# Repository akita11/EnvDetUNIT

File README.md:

# Envelope Detector (包絡線検波UNIT)

アナログ信号波形の包絡線（波形の外側の波形）を生成します。マイクなどからの音声信号の振幅を計測する場合などに便利です。Grove端子または3ピン端子で、マイク等の信号源とM5Stack等のマイコンとの間に接続して使用します。（[スイッチサイエンスで委託販売中](https://www.switch-science.com/products/9043)です）

表面

裏面

左側（CN1・J1、矢印の根本側）から信号源（マイクアンプの出力）を接続し、右側（CN2・J2、矢印の先端側）に包絡線波形が出力されるので、マイコン等に接続します。

## ピン配置

電源はCN1/J1/CN2/J2のいずれからのVDDへ+3.3V〜+5Vを与える。

### 入力側

- CN1(Groveコネクタ): アナログ入力1/アナログ入力2/VDD/GND （信号入力は標準で「アナログ入力1」で、JP1で「アナログ入力2」に切り替え可能
- J1（2.54mmピンヘッダ3ピン）: VDD/GND/アナログ入力

### 出力側

- CN2(Groveコネクタ): アナログ出力1/アナログ出力2/VDD/GND （信号出力は標準で「アナログ出力1」で、JP2で「アナログ出力2」に切り替え可能
- J2（2.54mmピンヘッダ3ピン）: VDD/GND/アナログ出力

## 包絡線検波とは？

音声信号などの変化が速い信号をマイコン等のA/D変換で取得する場合、A/D変換のタイミングと信号波形の変化のタイミングがあわないと、A/D変換値が波形の山の部分や谷の部分をバラバラに拾ってしまい（図中の◯）、正しく振幅を取得できません。

信号波形を包絡線検波回路に与えると、信号波形の外側をつないだ「包絡線」をつくることができます。（包絡線検波回路は、ダイオードを用いる半波整流回路にコンデンサの平滑回路を組み合わせたもの。厳密にはコンデンサの容量によって包絡線の波形が少し変わる。なおこのUNITでは、特に小さい振幅の信号も正しく扱えるようにオペアンプを使った理想ダイオードを使っています）

このようにして得られた包絡線波形に対してA/D変換を行えば、（ほぼ）正しく信号波形の振幅を取得することができます。

実際のマイク（M5StackマイクUNIT）の波形（黄色）と、このUNITの出力（水色）。

※なおこの回路の出力インピーダンスは高めなので、抵抗などの低インピーダンスの負荷を駆動すると波形が歪むことがあります。必要に応じて出力側にバッファ（ボルテージフォロア等）を使用してください。

## （オプション）時定数の調整

包絡線検波の回路の特性上、入力する信号波形の周波数によっては正しく包絡線を得られない場合があります。標準設定では1kHz前後の音声帯域の信号では、ほぼ正しい包絡線を得られますが、必要であれば回路の特性（時定数）を変更することができます。JP3をカットし、J3（2.54mmピンヘッダ2ピン）に適当な容量のコンデンサを接続します。標準では10uF（時定数は約160Hz）で、これより大きな容量のコンデンサを接続すると、包絡線の変化がより緩やかになります。

Aoutに100uFのコンデンサを接続したときの、マイクの波形（黄色）と、このUNITの出力（水色）。

## Author

Junichi Akita (akita@ifdl.jp, @akita11)

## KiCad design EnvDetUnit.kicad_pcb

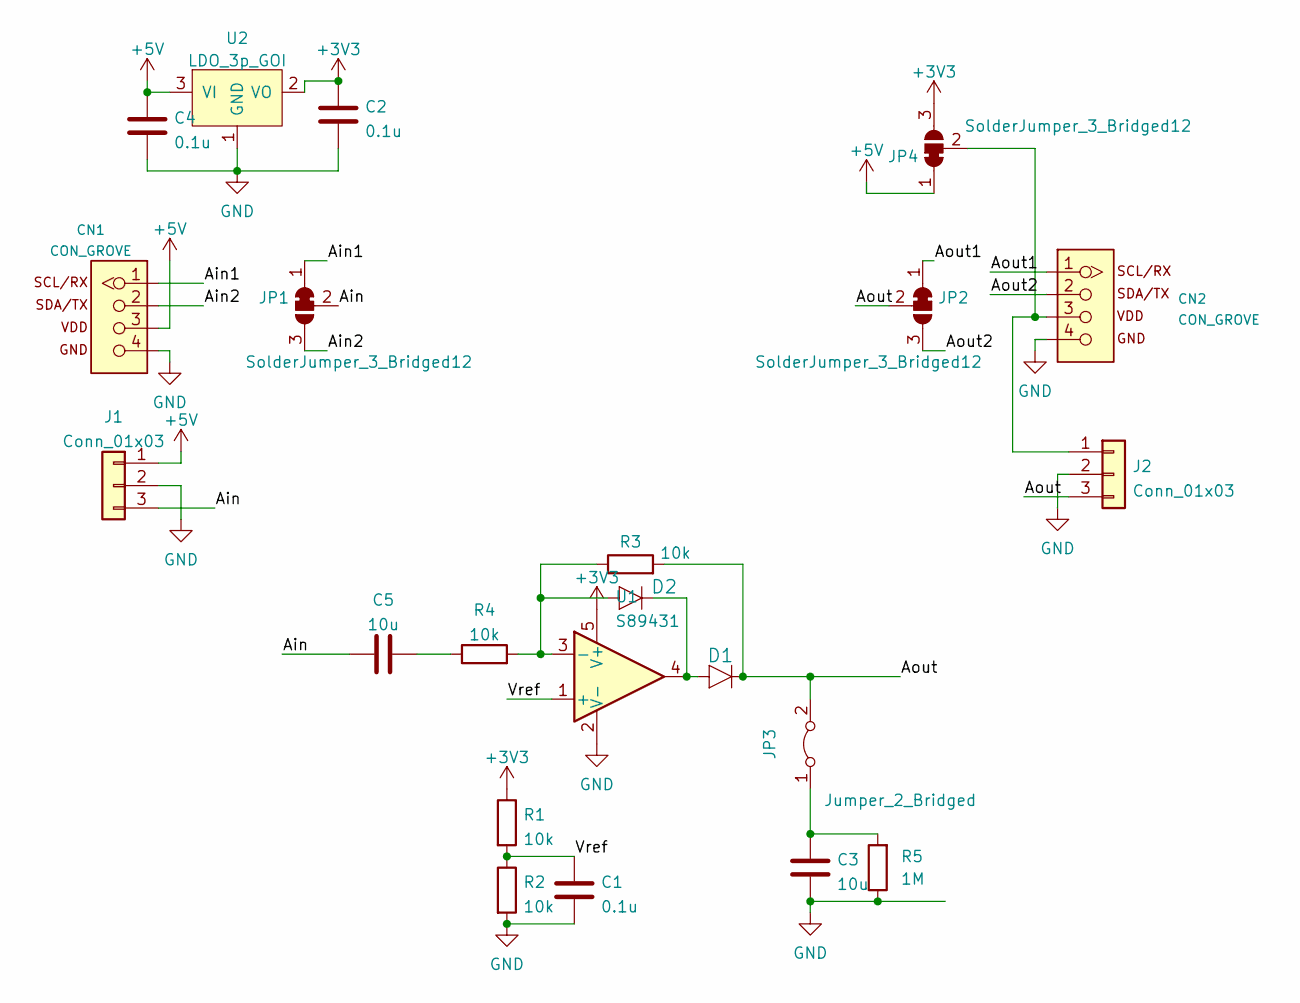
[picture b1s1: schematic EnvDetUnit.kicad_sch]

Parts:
C1, C2, C4: 0.1u; C_0603_1608Metric
C3, C5: 10u; C_0603_1608Metric
CN1, CN2: CON_GROVE; CON_GROVE_H
D1, D2: DIODE; D_SOD123FL
J1, J2: Conn_01x03; PinSocket_1x03_P2.54mm_Vertical
JP1, JP2, JP4: SolderJumper_3_Bridged12; SolderJumper-3_P1.3mm_Bridged2Bar12_Pad1.0x1.5mm_NumberLabe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
JP3: Jumper_2_Bridged; SolderJumper-2_P1.3mm_Bridged_Pad1.0x1.5mm
R1, R2, R3, R4: 10k; R_0603_1608Metric
R5: 1M; R_0603_1608Metric
U1: S89431; SOT-23-5
U2: LDO_3p_GOI; SOT-23

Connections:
+3V3: C2.1, JP4.3 (B), R1.1, U1.5 (V+), U2.2 (VO)
+5V: C4.1, CN1.3, J1.1, JP4.1 (A), U2.3 (VI)
/Ain: C5.1, J1.3, JP1.2 (C)
/Ain1: CN1.1, JP1.1 (A)
/Ain2: CN1.2, JP1.3 (B)
/Aout: D1.K, J2.3, JP2.2 (C), JP3.2 (B), R3.2
/Aout1: CN2.1, JP2.1 (A)
/Aout2: CN2.2, JP2.3 (B)
/Vref: C1.1, R1.2, R2.1, U1.1 (+)
GND: C1.2, C2.2, C3.2, C4.2, CN1.4, CN2.4, J1.2, J2.2, R2.2, R5.1, U1.2 (V-), U2.1 (GND)
unnamed: C3.1, JP3.1 (A), R5.2
unnamed: C5.2, R4.1
unnamed: CN2.3, J2.1, JP4.2 (C)
unnamed: D1.A, D2.K, U1.4
unnamed: D2.A, R3.1, R4.2, U1.3 (-)

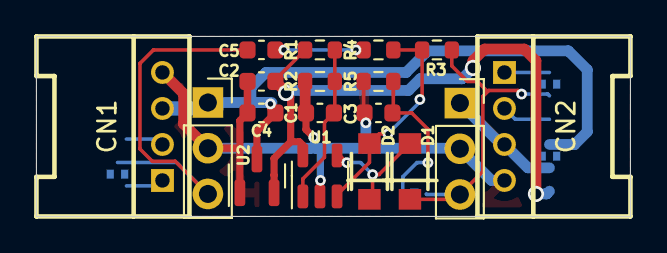
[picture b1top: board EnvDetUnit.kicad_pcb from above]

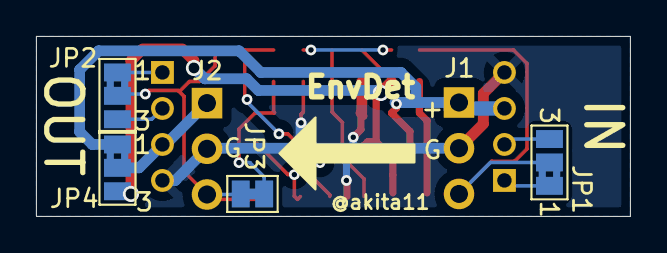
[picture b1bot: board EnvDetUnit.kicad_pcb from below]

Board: 2 copper layers, 33.0 x 10.0 mm, 22 parts (4 on the bottom side), 15 nets.

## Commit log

2023-06-20 add photo
2023-06-20 update PCB data
2023-06-21 change name
